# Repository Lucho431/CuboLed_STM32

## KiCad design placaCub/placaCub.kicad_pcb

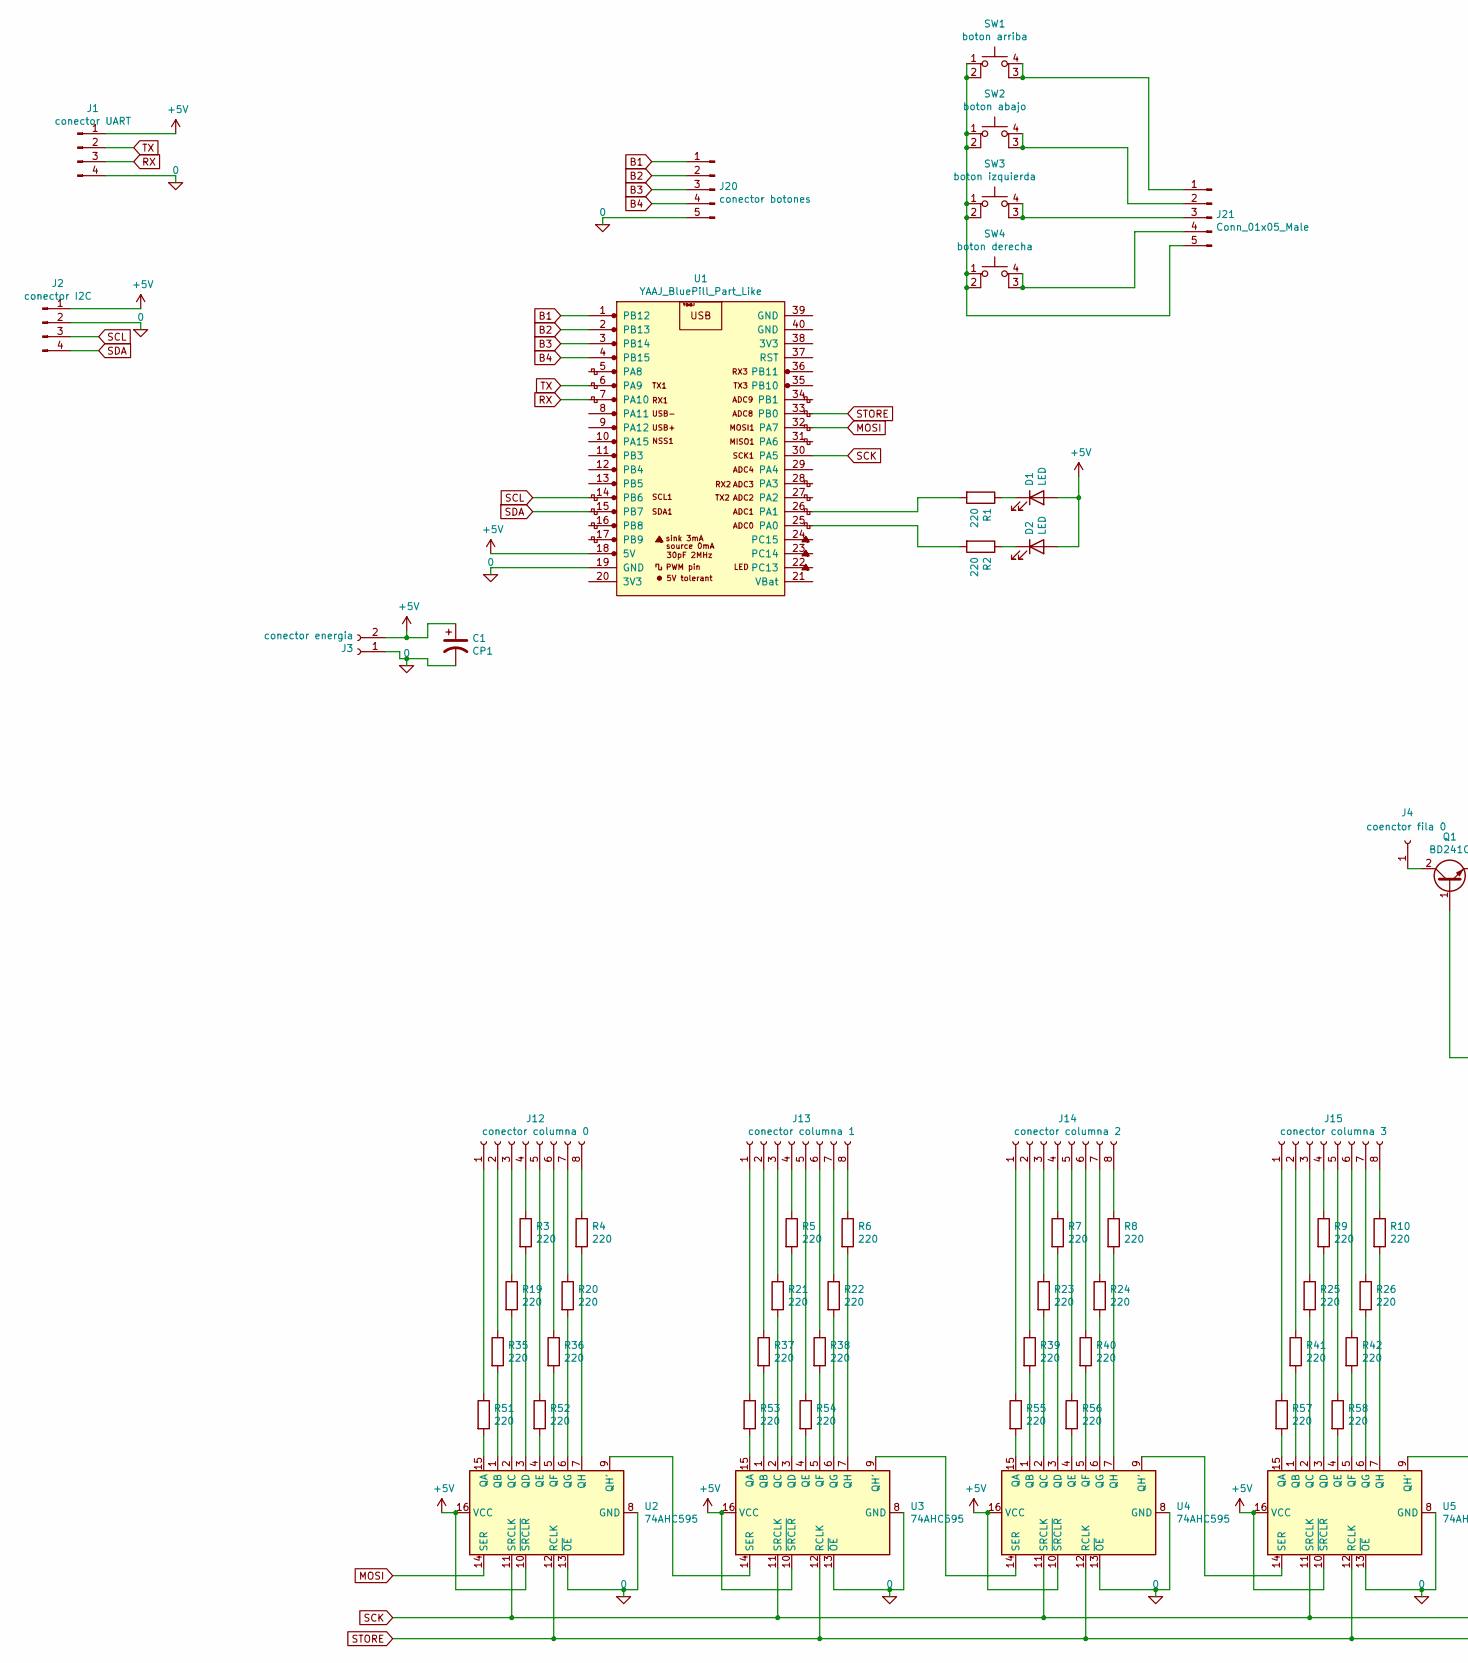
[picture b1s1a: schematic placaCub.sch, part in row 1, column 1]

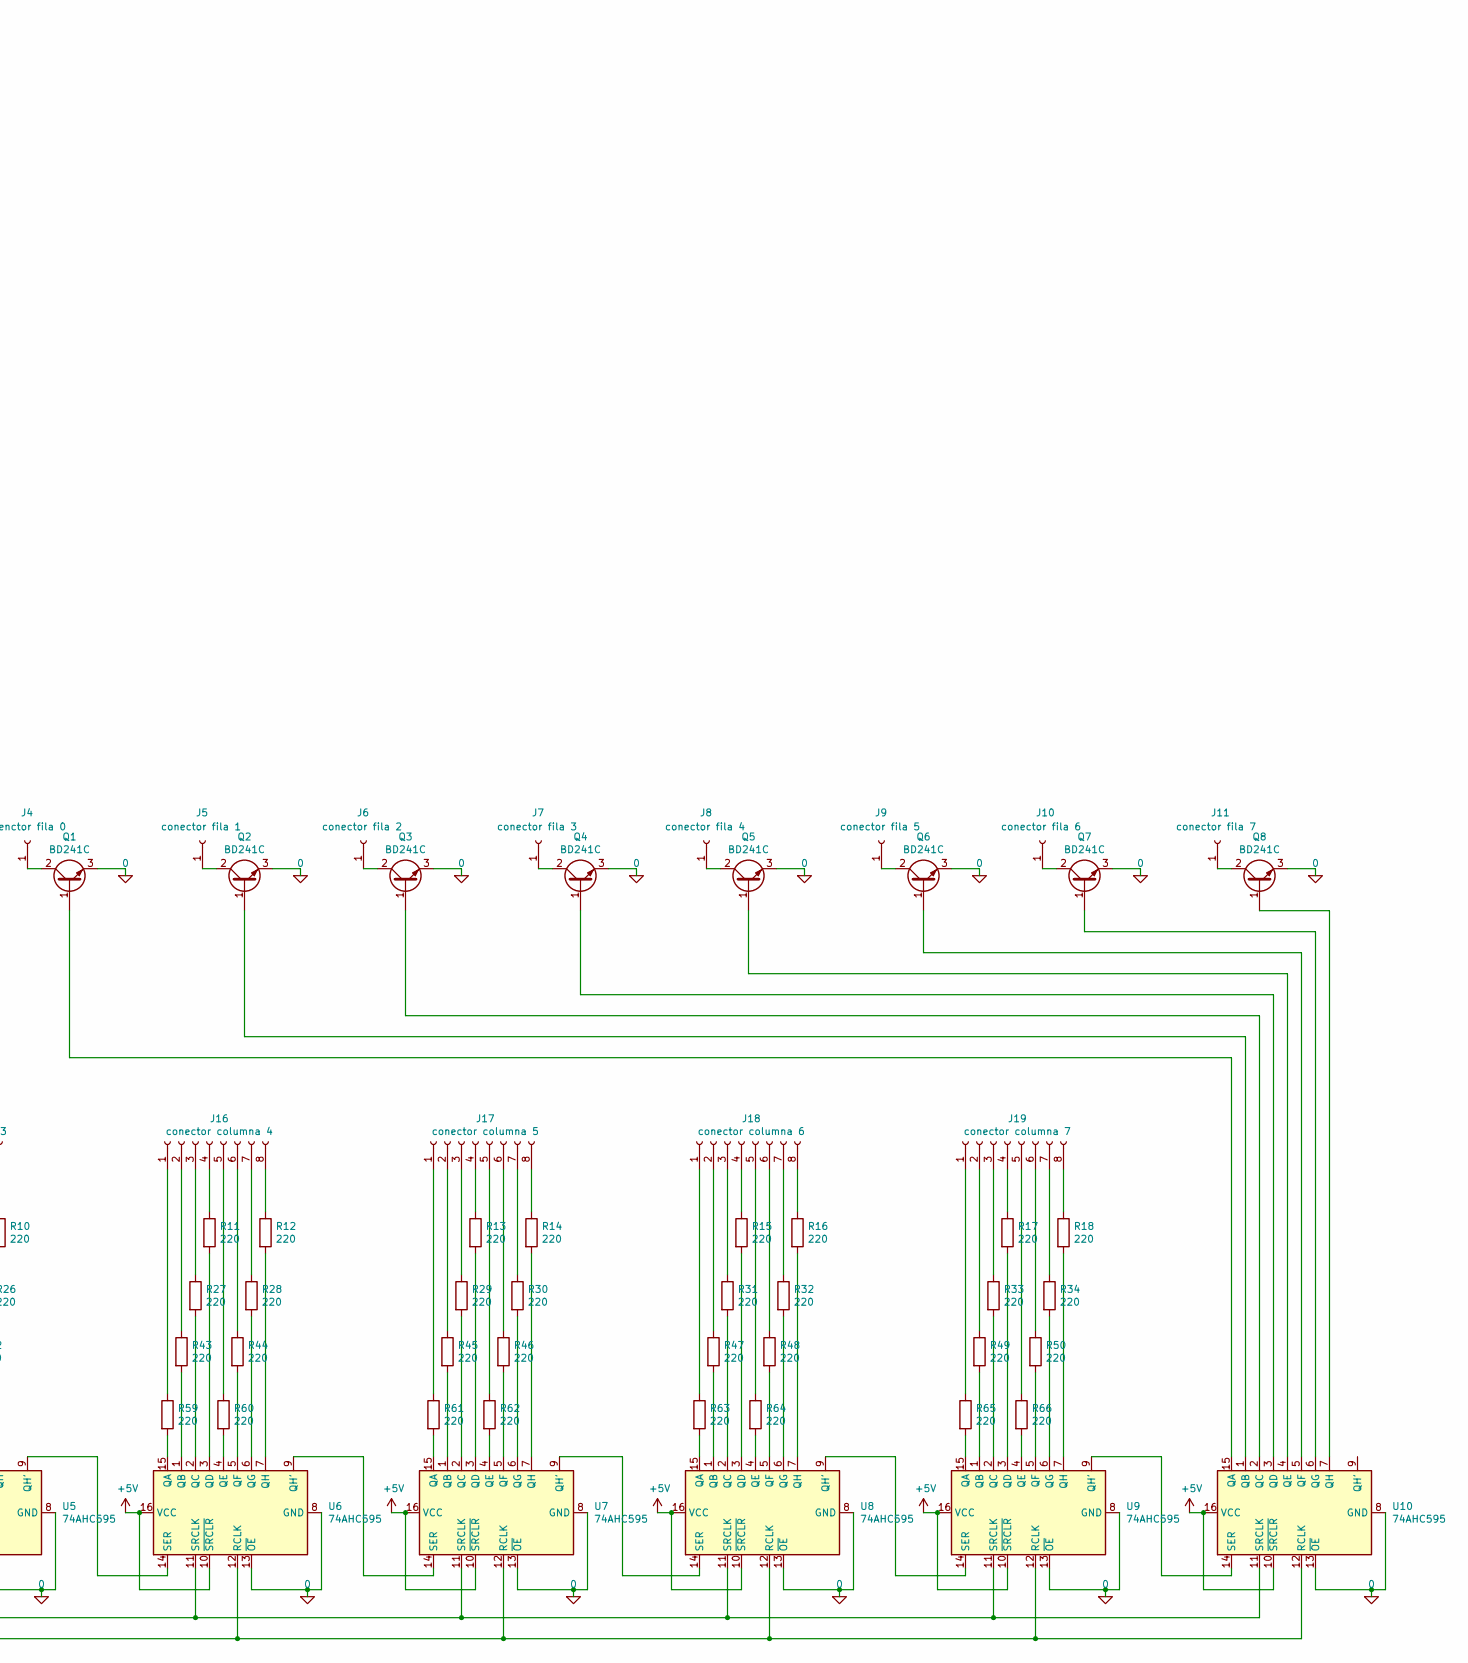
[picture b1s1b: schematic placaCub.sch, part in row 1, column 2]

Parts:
C1: CP1; CP_Radial_D8.0mm_P5.00mm
D1, D2: LED; LED_D3.0mm
J1: conector UART; Molex_KK-254_AE-6410-04A_1x04_P2.54mm_Vertical
J2: conector I2C; Molex_KK-254_AE-6410-04A_1x04_P2.54mm_Vertical
J3: conector energia; PhoenixContact_MSTBA_2,5_2-G_1x02_P5.00mm_Horizontal
J4: coenctor fila 0; PinHeader_1x01_P2.54mm_Vertical
J5: conector fila 1; PinHeader_1x01_P2.54mm_Vertical
J6: conector fila 2; PinHeader_1x01_P2.54mm_Vertical
J7: conector fila 3; PinHeader_1x01_P2.54mm_Vertical
J8: conector fila 4; PinHeader_1x01_P2.54mm_Vertical
J9: conector fila 5; PinHeader_1x01_P2.54mm_Vertical
J10: conector fila 6; PinHeader_1x01_P2.54mm_Vertical
J11: conector fila 7; PinHeader_1x01_P2.54mm_Vertical
J12: conector columna 0; Molex_KK-254_AE-6410-08A_1x08_P2.54mm_Vertical
J13: conector columna 1; Molex_KK-254_AE-6410-08A_1x08_P2.54mm_Vertical
J14: conector columna 2; Molex_KK-254_AE-6410-08A_1x08_P2.54mm_Vertical
J15: conector columna 3; Molex_KK-254_AE-6410-08A_1x08_P2.54mm_Vertical
J16: conector columna 4; Molex_KK-254_AE-6410-08A_1x08_P2.54mm_Vertical
J17: conector columna 5; Molex_KK-254_AE-6410-08A_1x08_P2.54mm_Vertical
J18: conector columna 6; Molex_KK-254_AE-6410-08A_1x08_P2.54mm_Vertical
J19: conector columna 7; Molex_KK-254_AE-6410-08A_1x08_P2.54mm_Vertical
J20: conector botones; Molex_KK-254_AE-6410-05A_1x05_P2.54mm_Vertical
J21: Conn_01x05_Male; Molex_KK-254_AE-6410-05A_1x05_P2.54mm_Vertical
Q1, Q2, Q3, Q4, Q5, Q6, Q7, Q8: BD241C; TO-220-3_Vertical
R1, R2, R3, R4, R5, R6, R7, R8, R9, R10, R11, R12, R13, R14, R15, R16, R17, R18, R19, R20, R21, R22, R23, R24, R25, R26, R27, R28, R29, R30, R31, R32, R33, R34, R35, R36, R37, R38, R39, R40, R41, R42, R43, R44, R45, R46, R47, R48, R49, R50, R51, R52, R53, R54, R55, R56, R57, R58, R59, R60, R61, R62, R63, R64, R65, R66: 220; R_Axial_DIN0207_L6.3mm_D2.5mm_P10.16mm_Horizontal
SW1: boton arriba; SW_PUSH_6mm_H7.3mm
SW2: boton abajo; SW_PUSH_6mm_H7.3mm
SW3: boton izquierda; SW_PUSH_6mm_H7.3mm
SW4: boton derecha; SW_PUSH_6mm_H7.3mm
U1: YAAJ_BluePill_Part_Like; YAAJ_BluePill_1
U2, U3, U4, U5, U6, U7, U8, U9, U10: 74AHC595; DIP-16_W7.62mm

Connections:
0: C1.2, J1.4, J2.2, J3.1, J20.5, Q1.3 (E), Q2.3 (E), Q3.3 (E), Q4.3 (E), Q5.3 (E), Q6.3 (E), Q7.3 (E), Q8.3 (E), U1.19 (GND), U2.8 (GND), U2.13 (~OE), U3.8 (GND), U3.13 (~OE), U4.8 (GND), U4.13 (~OE), U5.8 (GND), U5.13 (~OE), U6.8 (GND), U6.13 (~OE), U7.8 (GND), U7.13 (~OE), U8.8 (GND), U8.13 (~OE), U9.8 (GND), U9.13 (~OE), U10.8 (GND), U10.13 (~OE)
+5V: C1.1, D1.2 (A), D2.2 (A), J1.1, J2.1, J3.2, U1.18 (5V), U2.10 (~SRCLR), U2.16 (VCC), U3.10 (~SRCLR), U3.16 (VCC), U4.10 (~SRCLR), U4.16 (VCC), U5.10 (~SRCLR), U5.16 (VCC), U6.10 (~SRCLR), U6.16 (VCC), U7.10 (~SRCLR), U7.16 (VCC), U8.10 (~SRCLR), U8.16 (VCC), U9.10 (~SRCLR), U9.16 (VCC), U10.10 (~SRCLR), U10.16 (VCC)
B1: J20.1, U1.1 (PB12)
B2: J20.2, U1.2 (PB13)
B3: J20.3, U1.3 (PB14)
B4: J20.4, U1.4 (PB15)
MOSI: U1.32 (PA7), U2.14 (SER)
unnamed: D1.1 (K), R1.1
unnamed: D2.1 (K), R2.1
unnamed: J4.1, Q1.2 (C)
unnamed: J5.1, Q2.2 (C)
unnamed: J6.1, Q3.2 (C)
unnamed: J7.1, Q4.2 (C)
unnamed: J8.1, Q5.2 (C)
unnamed: J9.1, Q6.2 (C)
unnamed: J10.1, Q7.2 (C)
unnamed: J11.1, Q8.2 (C)
unnamed: J12.1, R51.1
unnamed: J12.2, R35.1
unnamed: J12.3, R19.1
unnamed: J12.4, R3.1
unnamed: J12.5, R52.1
unnamed: J12.6, R36.1
unnamed: J12.7, R20.1
unnamed: J12.8, R4.1
unnamed: J13.1, R53.1
unnamed: J13.2, R37.1
unnamed: J13.3, R21.1
unnamed: J13.4, R5.1
unnamed: J13.5, R54.1
unnamed: J13.6, R38.1
unnamed: J13.7, R22.1
unnamed: J13.8, R6.1
unnamed: J14.1, R55.1
unnamed: J14.2, R39.1
unnamed: J14.3, R23.1
unnamed: J14.4, R7.1
unnamed: J14.5, R56.1
unnamed: J14.6, R40.1
unnamed: J14.7, R24.1
unnamed: J14.8, R8.1
unnamed: J15.1, R57.1
unnamed: J15.2, R41.1
unnamed: J15.3, R25.1
unnamed: J15.4, R9.1
unnamed: J15.5, R58.1
unnamed: J15.6, R42.1
unnamed: J15.7, R26.1
unnamed: J15.8, R10.1
unnamed: J16.1, R59.1
unnamed: J16.2, R43.1
unnamed: J16.3, R27.1
unnamed: J16.4, R11.1
unnamed: J16.5, R60.1
unnamed: J16.6, R44.1
unnamed: J16.7, R28.1
unnamed: J16.8, R12.1
unnamed: J17.1, R61.1
unnamed: J17.2, R45.1
unnamed: J17.3, R29.1
unnamed: J17.4, R13.1
unnamed: J17.5, R62.1
unnamed: J17.6, R46.1
unnamed: J17.7, R30.1
unnamed: J17.8, R14.1
unnamed: J18.1, R63.1
unnamed: J18.2, R47.1
unnamed: J18.3, R31.1
unnamed: J18.4, R15.1
unnamed: J18.5, R64.1
unnamed: J18.6, R48.1
unnamed: J18.7, R32.1
unnamed: J18.8, R16.1
unnamed: J19.1, R65.1
unnamed: J19.2, R49.1
unnamed: J19.3, R33.1
unnamed: J19.4, R17.1
unnamed: J19.5, R66.1
unnamed: J19.6, R50.1
unnamed: J19.7, R34.1
unnamed: J19.8, R18.1
unnamed: J21.1, SW1.3 (K), SW1.4 (A)
unnamed: J21.2, SW2.3 (K), SW2.4 (A)
unnamed: J21.3, SW3.3 (K), SW3.4 (A)
unnamed: J21.4, SW4.3 (K), SW4.4 (A)
unnamed: J21.5, SW1.1, SW1.2, SW2.1, SW2.2, SW3.1, SW3.2, SW4.1, SW4.2
unnamed: Q1.1 (B), U10.15 (QA)
unnamed: Q2.1 (B), U10.1 (QB)
unnamed: Q3.1 (B), U10.2 (QC)
unnamed: Q4.1 (B), U10.3 (QD)
unnamed: Q5.1 (B), U10.4 (QE)
unnamed: Q6.1 (B), U10.5 (QF)
unnamed: Q7.1 (B), U10.6 (QG)
unnamed: Q8.1 (B), U10.7 (QH)
unnamed: R1.2, U1.26 (PA1)
unnamed: R2.2, U1.25 (PA0)
unnamed: R3.2, U2.3 (QD)
unnamed: R4.2, U2.7 (QH)
unnamed: R5.2, U3.3 (QD)
unnamed: R6.2, U3.7 (QH)
unnamed: R7.2, U4.3 (QD)
unnamed: R8.2, U4.7 (QH)
unnamed: R9.2, U5.3 (QD)
unnamed: R10.2, U5.7 (QH)
unnamed: R11.2, U6.3 (QD)
unnamed: R12.2, U6.7 (QH)
unnamed: R13.2, U7.3 (QD)
unnamed: R14.2, U7.7 (QH)
unnamed: R15.2, U8.3 (QD)
unnamed: R16.2, U8.7 (QH)
unnamed: R17.2, U9.3 (QD)
unnamed: R18.2, U9.7 (QH)
unnamed: R19.2, U2.2 (QC)
unnamed: R20.2, U2.6 (QG)
unnamed: R21.2, U3.2 (QC)
unnamed: R22.2, U3.6 (QG)
unnamed: R23.2, U4.2 (QC)
unnamed: R24.2, U4.6 (QG)
unnamed: R25.2, U5.2 (QC)
unnamed: R26.2, U5.6 (QG)
unnamed: R27.2, U6.2 (QC)
unnamed: R28.2, U6.6 (QG)
unnamed: R29.2, U7.2 (QC)
unnamed: R30.2, U7.6 (QG)
unnamed: R31.2, U8.2 (QC)
unnamed: R32.2, U8.6 (QG)
unnamed: R33.2, U9.2 (QC)
unnamed: R34.2, U9.6 (QG)
unnamed: R35.2, U2.1 (QB)
unnamed: R36.2, U2.5 (QF)
unnamed: R37.2, U3.1 (QB)
unnamed: R38.2, U3.5 (QF)
unnamed: R39.2, U4.1 (QB)
unnamed: R40.2, U4.5 (QF)
unnamed: R41.2, U5.1 (QB)
unnamed: R42.2, U5.5 (QF)
unnamed: R43.2, U6.1 (QB)
unnamed: R44.2, U6.5 (QF)
unnamed: R45.2, U7.1 (QB)
unnamed: R46.2, U7.5 (QF)
unnamed: R47.2, U8.1 (QB)
unnamed: R48.2, U8.5 (QF)
unnamed: R49.2, U9.1 (QB)
unnamed: R50.2, U9.5 (QF)
unnamed: R51.2, U2.15 (QA)
unnamed: R52.2, U2.4 (QE)
unnamed: R53.2, U3.15 (QA)
unnamed: R54.2, U3.4 (QE)
unnamed: R55.2, U4.15 (QA)
unnamed: R56.2, U4.4 (QE)
unnamed: R57.2, U5.15 (QA)
unnamed: R58.2, U5.4 (QE)
unnamed: R59.2, U6.15 (QA)
unnamed: R60.2, U6.4 (QE)
unnamed: R61.2, U7.15 (QA)
unnamed: R62.2, U7.4 (QE)
unnamed: R63.2, U8.15 (QA)
unnamed: R64.2, U8.4 (QE)
unnamed: R65.2, U9.15 (QA)
unnamed: R66.2, U9.4 (QE)
unnamed: U2.9 (QH'), U3.14 (SER)
unnamed: U3.9 (QH'), U4.14 (SER)
unnamed: U4.9 (QH'), U5.14 (SER)
unnamed: U5.9 (QH'), U6.14 (SER)
unnamed: U6.9 (QH'), U7.14 (SER)
unnamed: U7.9 (QH'), U8.14 (SER)
unnamed: U8.9 (QH'), U9.14 (SER)
unnamed: U9.9 (QH'), U10.14 (SER)
RX: J1.3, U1.7 (PA10)
SCK: U1.30 (PA5), U2.11 (SRCLK), U3.11 (SRCLK), U4.11 (SRCLK), U5.11 (SRCLK), U6.11 (SRCLK), U7.11 (SRCLK), U8.11 (SRCLK), U9.11 (SRCLK), U10.11 (SRCLK)
SCL: J2.3, U1.14 (PB6)
SDA: J2.4, U1.15 (PB7)
STORE: U1.33 (PB0), U2.12 (RCLK), U3.12 (RCLK), U4.12 (RCLK), U5.12 (RCLK), U6.12 (RCLK), U7.12 (RCLK), U8.12 (RCLK), U9.12 (RCLK), U10.12 (RCLK)
TX: J1.2, U1.6 (PA9)

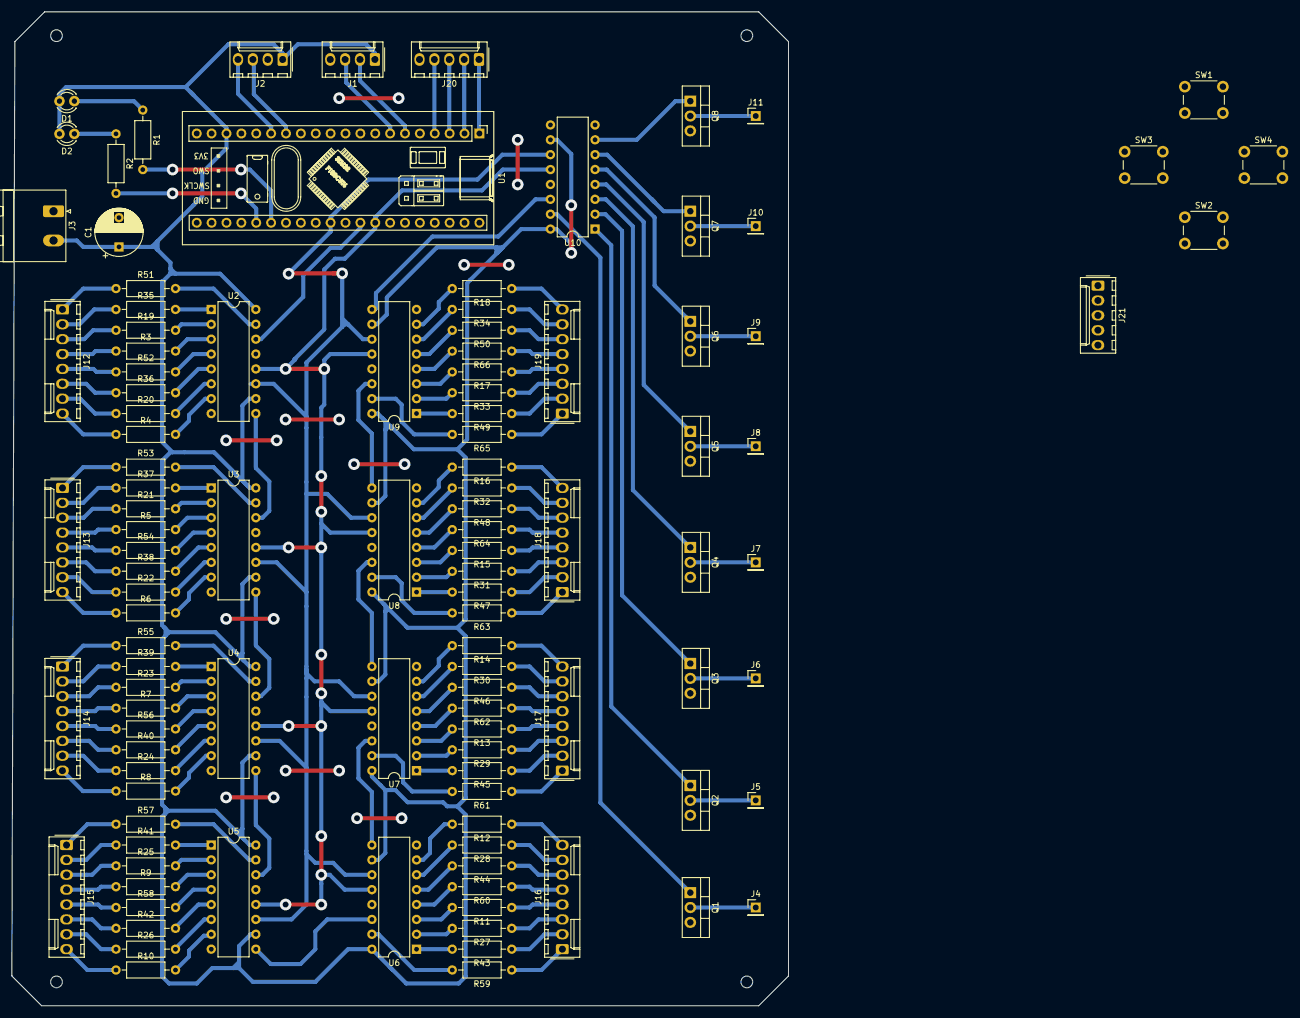
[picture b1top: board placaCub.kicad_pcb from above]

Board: 2 copper layers, 132.6 x 169.7 mm, 112 parts (0 on the bottom side), 170 nets.

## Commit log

2022-03-26 primer commit
2022-03-26 archivos agregados al repositorio
2022-03-26 diseño del pcb
2022-03-27 avances en el diseño del PCB
2022-03-28 nuevo update 28/03/2022
2022-04-01 contornos de la placa realizados
2022-04-07 archivo CNC en proceso
2022-04-08 archivo CNC completado
2022-04-11 fotos de los puentes
2022-04-13 cambios en el codigo original
2022-04-15 proyecto en STM32CubeIDE generado
2022-05-27 programa probado en plaqueta
2022-05-30 timer agregado
2022-06-13 modelos para imprimir en 3D
2022-09-18 cubo andando
2022-11-12 desarrollo del efecto fuegoArtificial
2022-11-12 reubicacion de archivo fuegoArtificial.c
2022-11-12 efecto de fuegos artificiales agregado
2023-01-24 comienzo de menus
2023-03-10 inicia juego block out
2023-03-13 avances en la logica del block out
2023-03-14 proyecto de kicad actualizado
2023-03-14 prototipo a ciegas de block out
2023-03-15 primeros errores en block out
2023-03-15 correcciones en la biblioteca blockOut
2023-03-16 transcripcion de codigo block out
2023-03-16 continuan las pruebas del block out
2023-03-17 preparado para pirmer prueba en cubo
2023-03-18 primera correccion en el cubo
2023-03-19 mas cambios en la implementacion del block out
2023-03-21 caida de fichas en block out correcta
2023-03-22 error detectado al girar piezas
2023-03-22 blockout agregado al reparto de efectos
2023-03-22 blockout agregado al reparto de efectos resubido
2024-01-18 notas agregadas para revision del blockOut
2024-01-25 blockOut con bugs de piso y de pos_piezaX corregidos
2024-05-13 demo y menu modificados para gv0
2026-01-19 mejoras generales en todo el funcionamiento del cubo
